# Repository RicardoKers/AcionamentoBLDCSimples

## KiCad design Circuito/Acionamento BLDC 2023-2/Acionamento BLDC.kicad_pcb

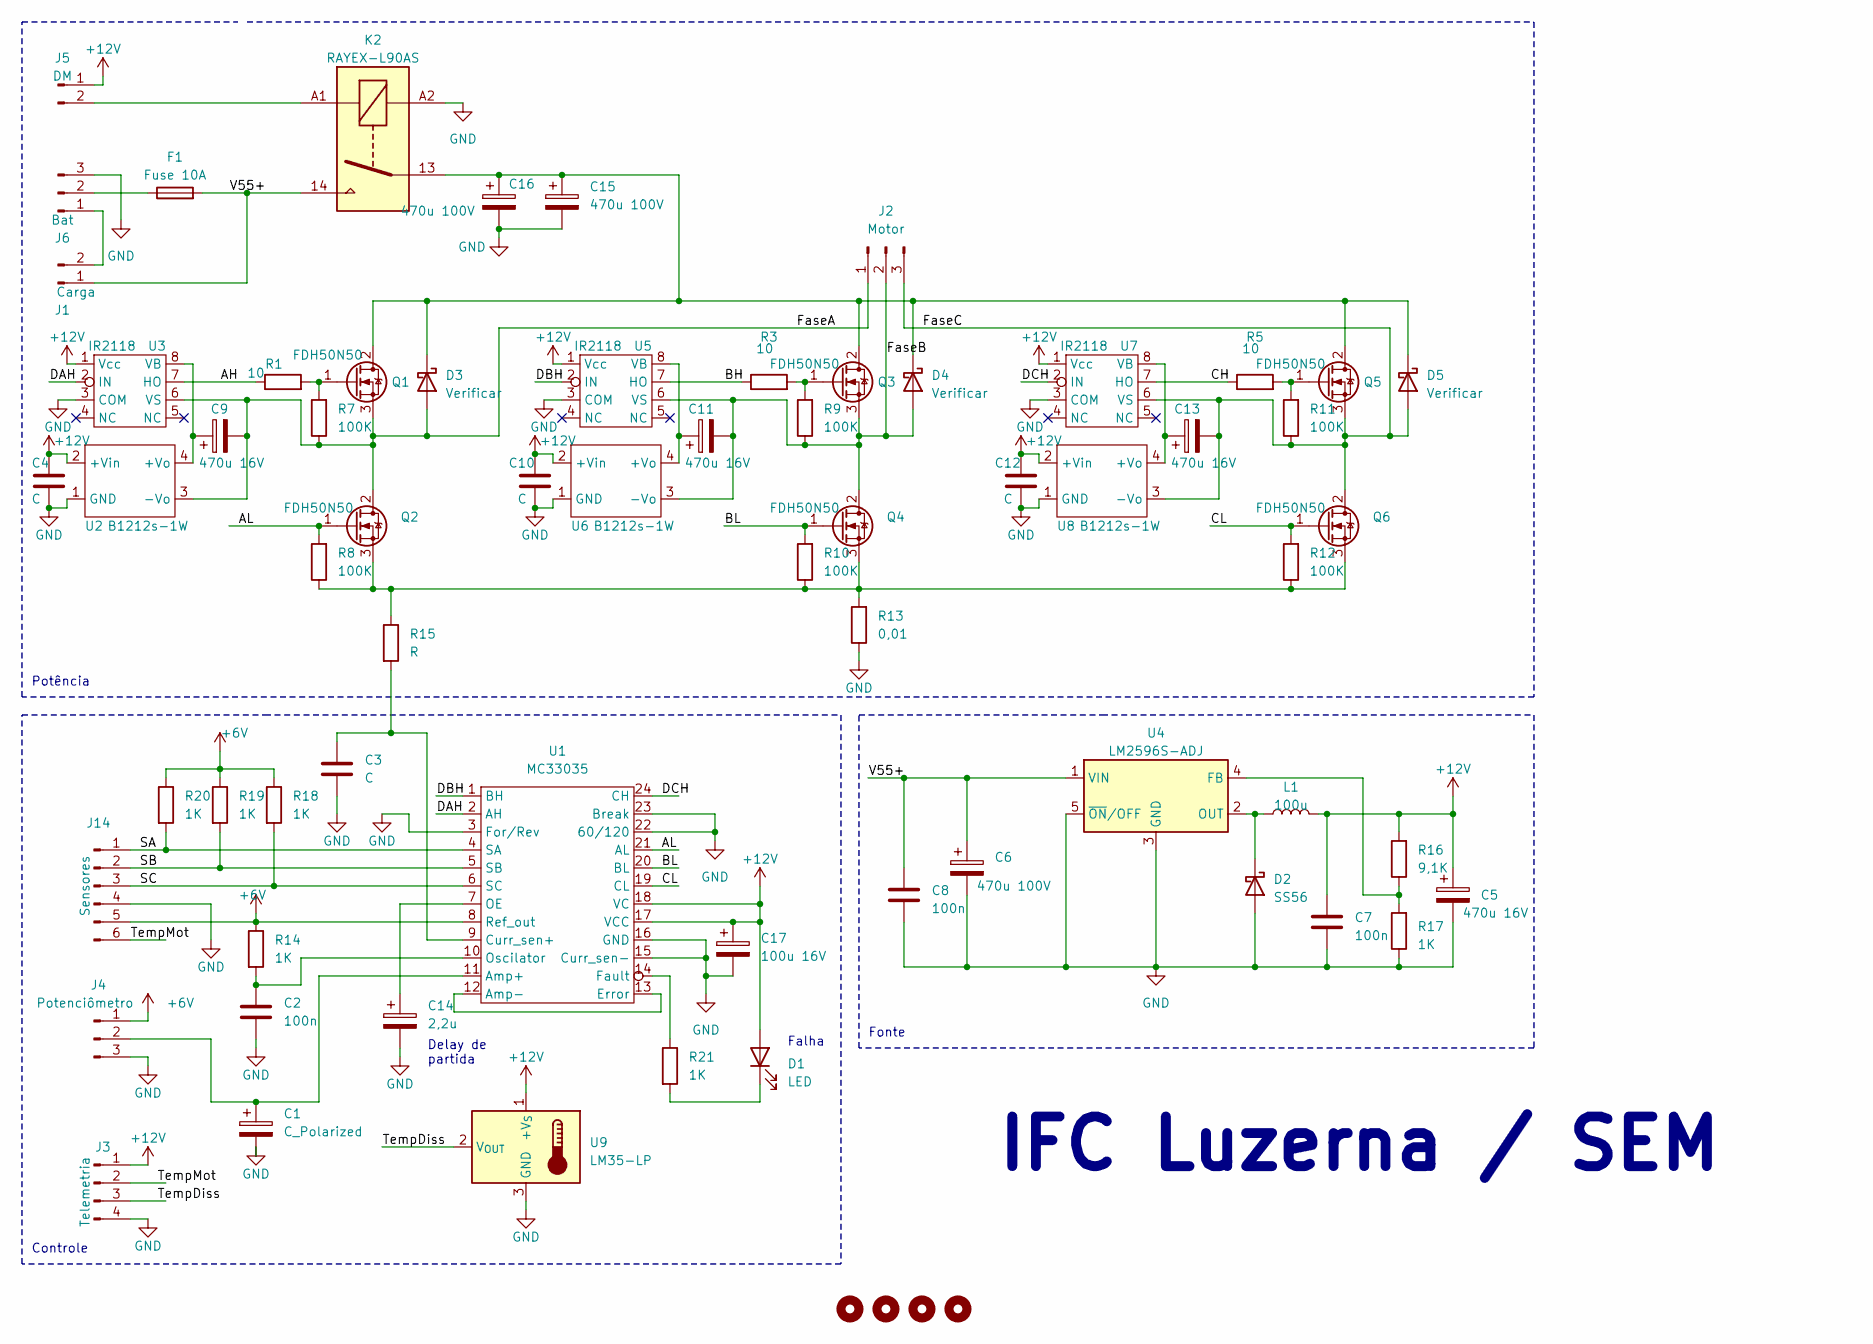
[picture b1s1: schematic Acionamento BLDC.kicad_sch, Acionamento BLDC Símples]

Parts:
C1: C_Polarized; CP_Radial_D8.0mm_P3.50mm
C2: 100n; C_Disc_D9.0mm_W2.5mm_P5.00mm
C3, C4, C10, C12: C; C_Disc_D9.0mm_W2.5mm_P5.00mm
C5, C9, C11, C13: 470u 16V; CP_Radial_D8.0mm_P3.50mm
C6, C15, C16: 470u 100V; CP_Radial_D17.0mm_P7.50mm
C7, C8: 100n; C_Axial_L5.1mm_D3.1mm_P7.50mm_Horizontal
C14: 2,2u; CP_Radial_D4.0mm_P2.00mm
C17: 100u 16V; CP_Radial_D5.0mm_P2.50mm
D1: LED; LED_D5.0mm
D2: SS56; D_3220_8050Metric_Pad2.65x5.15mm_HandSolder
D3, D4, D5: Verificar; TO-220-2_Vertical
F1: Fuse 10A; Fuse_Blade_ATO_directSolder
H1, H2, H3, H4: MountingHole; MountingHole_3.5mm
J1: Carga; PhoenixContact_MSTBA_2,5_2-G-5,08_1x02_P5.08mm_Horizontal
J2: Motor; PhoenixContact_MSTBA_2,5_3-G-5,08_1x03_P5.08mm_Horizontal
J3: Telemetria; PhoenixContact_MC_1,5_4-G-3.81_1x04_P3.81mm_Horizontal
J4: Potenciômetro; PhoenixContact_MC_1,5_3-G-3.81_1x03_P3.81mm_Horizontal
J5: DM; PhoenixContact_MC_1,5_2-G-3.81_1x02_P3.81mm_Horizontal
J6: Bat; PhoenixContact_MSTBA_2,5_3-G-5,08_1x03_P5.08mm_Horizontal
J14: Sensores; PhoenixContact_MC_1,5_6-G-3.81_1x06_P3.81mm_Horizontal
K2: RAYEX-L90AS; Relay_SPST_RAYEX-L90AS
L1: 100u; L_12x12mm_H6mm
Q1, Q2, Q3, Q4, Q5, Q6: FDH50N50; TO-247-3_Vertical
R1, R3, R5: 10; R_Axial_DIN0207_L6.3mm_D2.5mm_P10.16mm_Horizontal
R7, R8, R9, R10, R11, R12: 100K; R_Axial_DIN0207_L6.3mm_D2.5mm_P10.16mm_Horizontal
R13: 0,01; R_Axial_Power_L25.0mm_W9.0mm_P27.94mm
R14, R17, R18, R19, R20, R21: 1K; R_Axial_DIN0207_L6.3mm_D2.5mm_P10.16mm_Horizontal
R15: R; R_Axial_DIN0207_L6.3mm_D2.5mm_P10.16mm_Horizontal
R16: 9,1K; R_Axial_DIN0207_L6.3mm_D2.5mm_P10.16mm_Horizontal
U1: MC33035; DIP-24_W7.62mm_LongPads
U2, U6, U8: B1212s-1W
U3, U5, U7: IR2118; DIP-8_W7.62mm_LongPads
U4: LM2596S-ADJ; TO-263-5_TabPin3
U9: LM35-LP; TO-92_Inline

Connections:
+6V: J4.1, J14.5, R14.1, R18.1, R19.1, R20.1, U1.8 (Ref_out)
+12V: C4.1, C5.1, C7.1, C10.1, C12.1, C17.1, D1.2 (A), J3.1, J5.1, L1.2, R16.2, U1.17 (VCC), U1.18 (VC), U2.2 (+Vin), U3.1 (Vcc), U5.1 (Vcc), U6.2 (+Vin), U7.1 (Vcc), U8.2 (+Vin), U9.1 (+V_{S})
/AH: R1.1, U3.7 (HO)
/AL: Q2.1 (G), R8.2, U1.21 (AL)
/BH: R3.1, U5.7 (HO)
/BL: Q4.1 (G), R10.2, U1.20 (BL)
/CH: R5.1, U7.7 (HO)
/CL: Q6.1 (G), R12.2, U1.19 (CL)
/DAH: U1.2 (AH), U3.2 (IN)
/DBH: U1.1 (BH), U5.2 (IN)
/DCH: U1.24 (CH), U7.2 (IN)
/FaseA: C9.2, D3.2 (A), J2.1, Q1.3 (S), Q2.2 (D), R7.1, U2.3 (-Vo), U3.6 (VS)
/FaseB: C11.2, D4.2 (A), J2.2, Q3.3 (S), Q4.2 (D), R9.1, U5.6 (VS), U6.3 (-Vo)
/FaseC: C13.2, D5.2 (A), J2.3, Q5.3 (S), Q6.2 (D), R11.1, U7.6 (VS), U8.3 (-Vo)
/SA: J14.1, R20.2, U1.4 (SA)
/SB: J14.2, R19.2, U1.5 (SB)
/SC: J14.3, R18.2, U1.6 (SC)
/TempDiss: J3.3, U9.2 (V_{OUT})
/TempMot: J3.2, J14.6
/V55+: C6.1, C8.1, F1.2, J1.1, K2.14, U4.1 (VIN)
GND: C1.2, C2.2, C3.2, C4.2, C5.2, C6.2, C7.2, C8.2, C10.2, C12.2, C14.2, C15.2, C16.2, C17.2, D2.2 (A), J3.4, J4.3, J6.3, J14.4, K2.A2, R13.1, R17.1, U1.3 (For/Rev), U1.15 (Curr_sen-), U1.16 (GND), U1.22 (60/120), U1.23 (Break), U2.1 (GND), U3.3 (COM), U4.3 (GND), U4.5 (~ON/OFF), U5.3 (COM), U6.1 (GND), U7.3 (COM), U8.1 (GND), U9.3 (GND)
unnamed: D1.1 (K), R21.2
unnamed: D2.1 (K), L1.1, U4.2 (OUT)
unnamed: C15.1, C16.1, D3.1 (K), D4.1 (K), D5.1 (K), K2.13, Q1.2 (D), Q3.2 (D), Q5.2 (D)
unnamed: J1.2, J6.1
unnamed: C1.1, J4.2, U1.11 (Amp+)
unnamed: J5.2, K2.A1
unnamed: F1.1, J6.2
unnamed: Q1.1 (G), R1.2, R7.2
unnamed: Q2.3 (S), Q4.3 (S), Q6.3 (S), R8.1, R10.1, R12.1, R13.2, R15.1
unnamed: Q3.1 (G), R3.2, R9.2
unnamed: Q5.1 (G), R5.2, R11.2
unnamed: U1.12 (Amp-), U1.13 (Error)
unnamed: C3.1, R15.2, U1.9 (Curr_sen+)
unnamed: R21.1, U1.14 (Fault)
unnamed: C14.1, U1.7 (OE)
unnamed: C2.1, R14.2, U1.10 (Oscilator)
unnamed: C9.1, U2.4 (+Vo), U3.8 (VB)
unnamed: R16.1, R17.2, U4.4 (FB)
unnamed: C11.1, U5.8 (VB), U6.4 (+Vo)
unnamed: C13.1, U7.8 (VB), U8.4 (+Vo)

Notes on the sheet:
IFC Luzerna / SEM
Potência
Fonte
Controle
Delay de partida
Falha

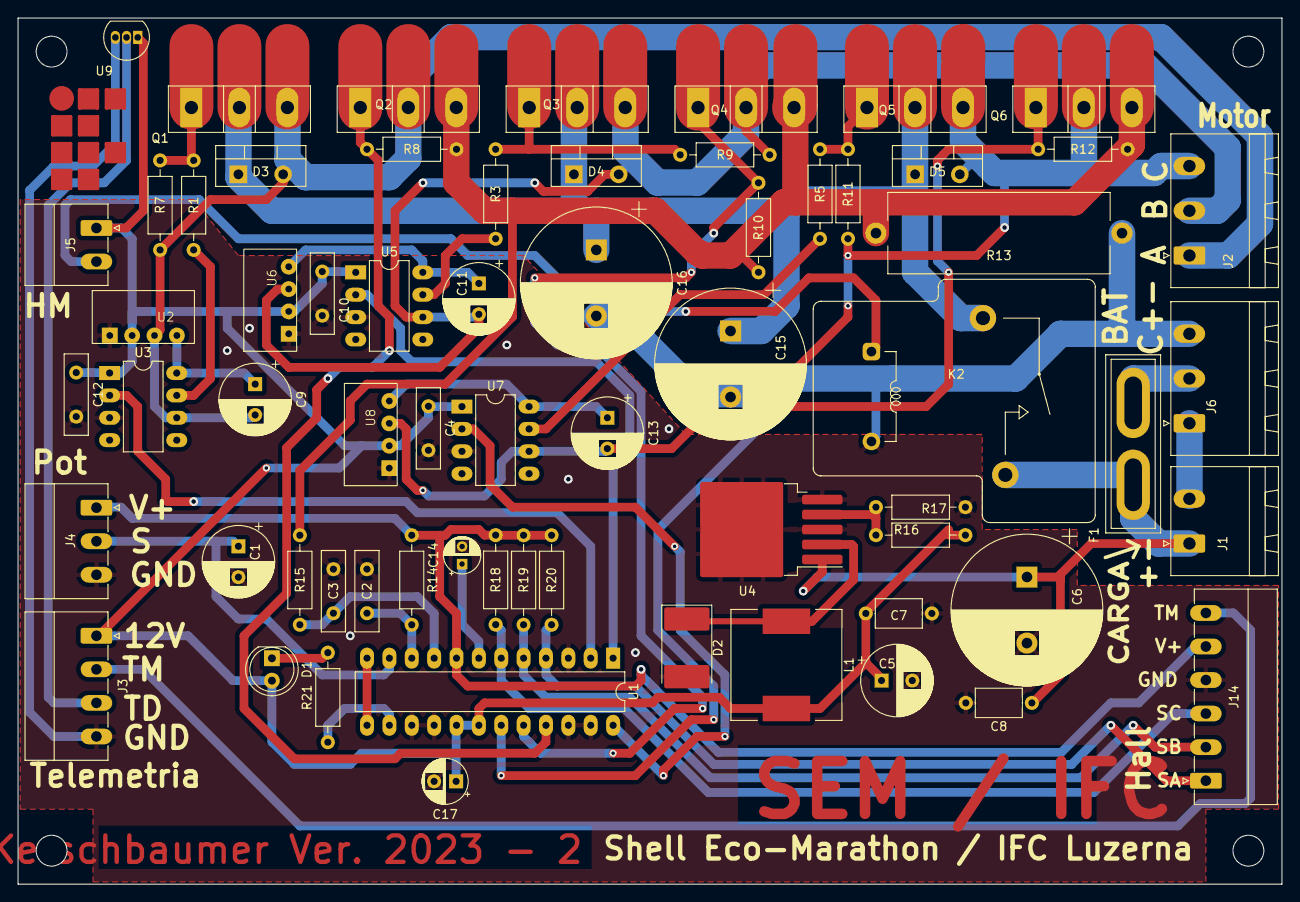
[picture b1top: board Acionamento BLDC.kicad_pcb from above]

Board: 2 copper layers, 143.5 x 98.3 mm, 69 parts (0 on the bottom side), 41 nets.

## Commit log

2023-02-28 Start Vercion
2023-03-22 Versão 2023
2023-04-18 Versão 2023-2
